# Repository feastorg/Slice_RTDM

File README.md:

# Slice RTDM

Slice for RTD (resistive temperature device) measurement using the MAX31865 chip.

## Introduction

[Short introduction on the project.]

## Usage

[Explain how to use the project. Include examples and screenshots if applicable.]

## Documentation

Please refer to the [docs](/docs) for more info.

---

<div align="center">
  
</div>

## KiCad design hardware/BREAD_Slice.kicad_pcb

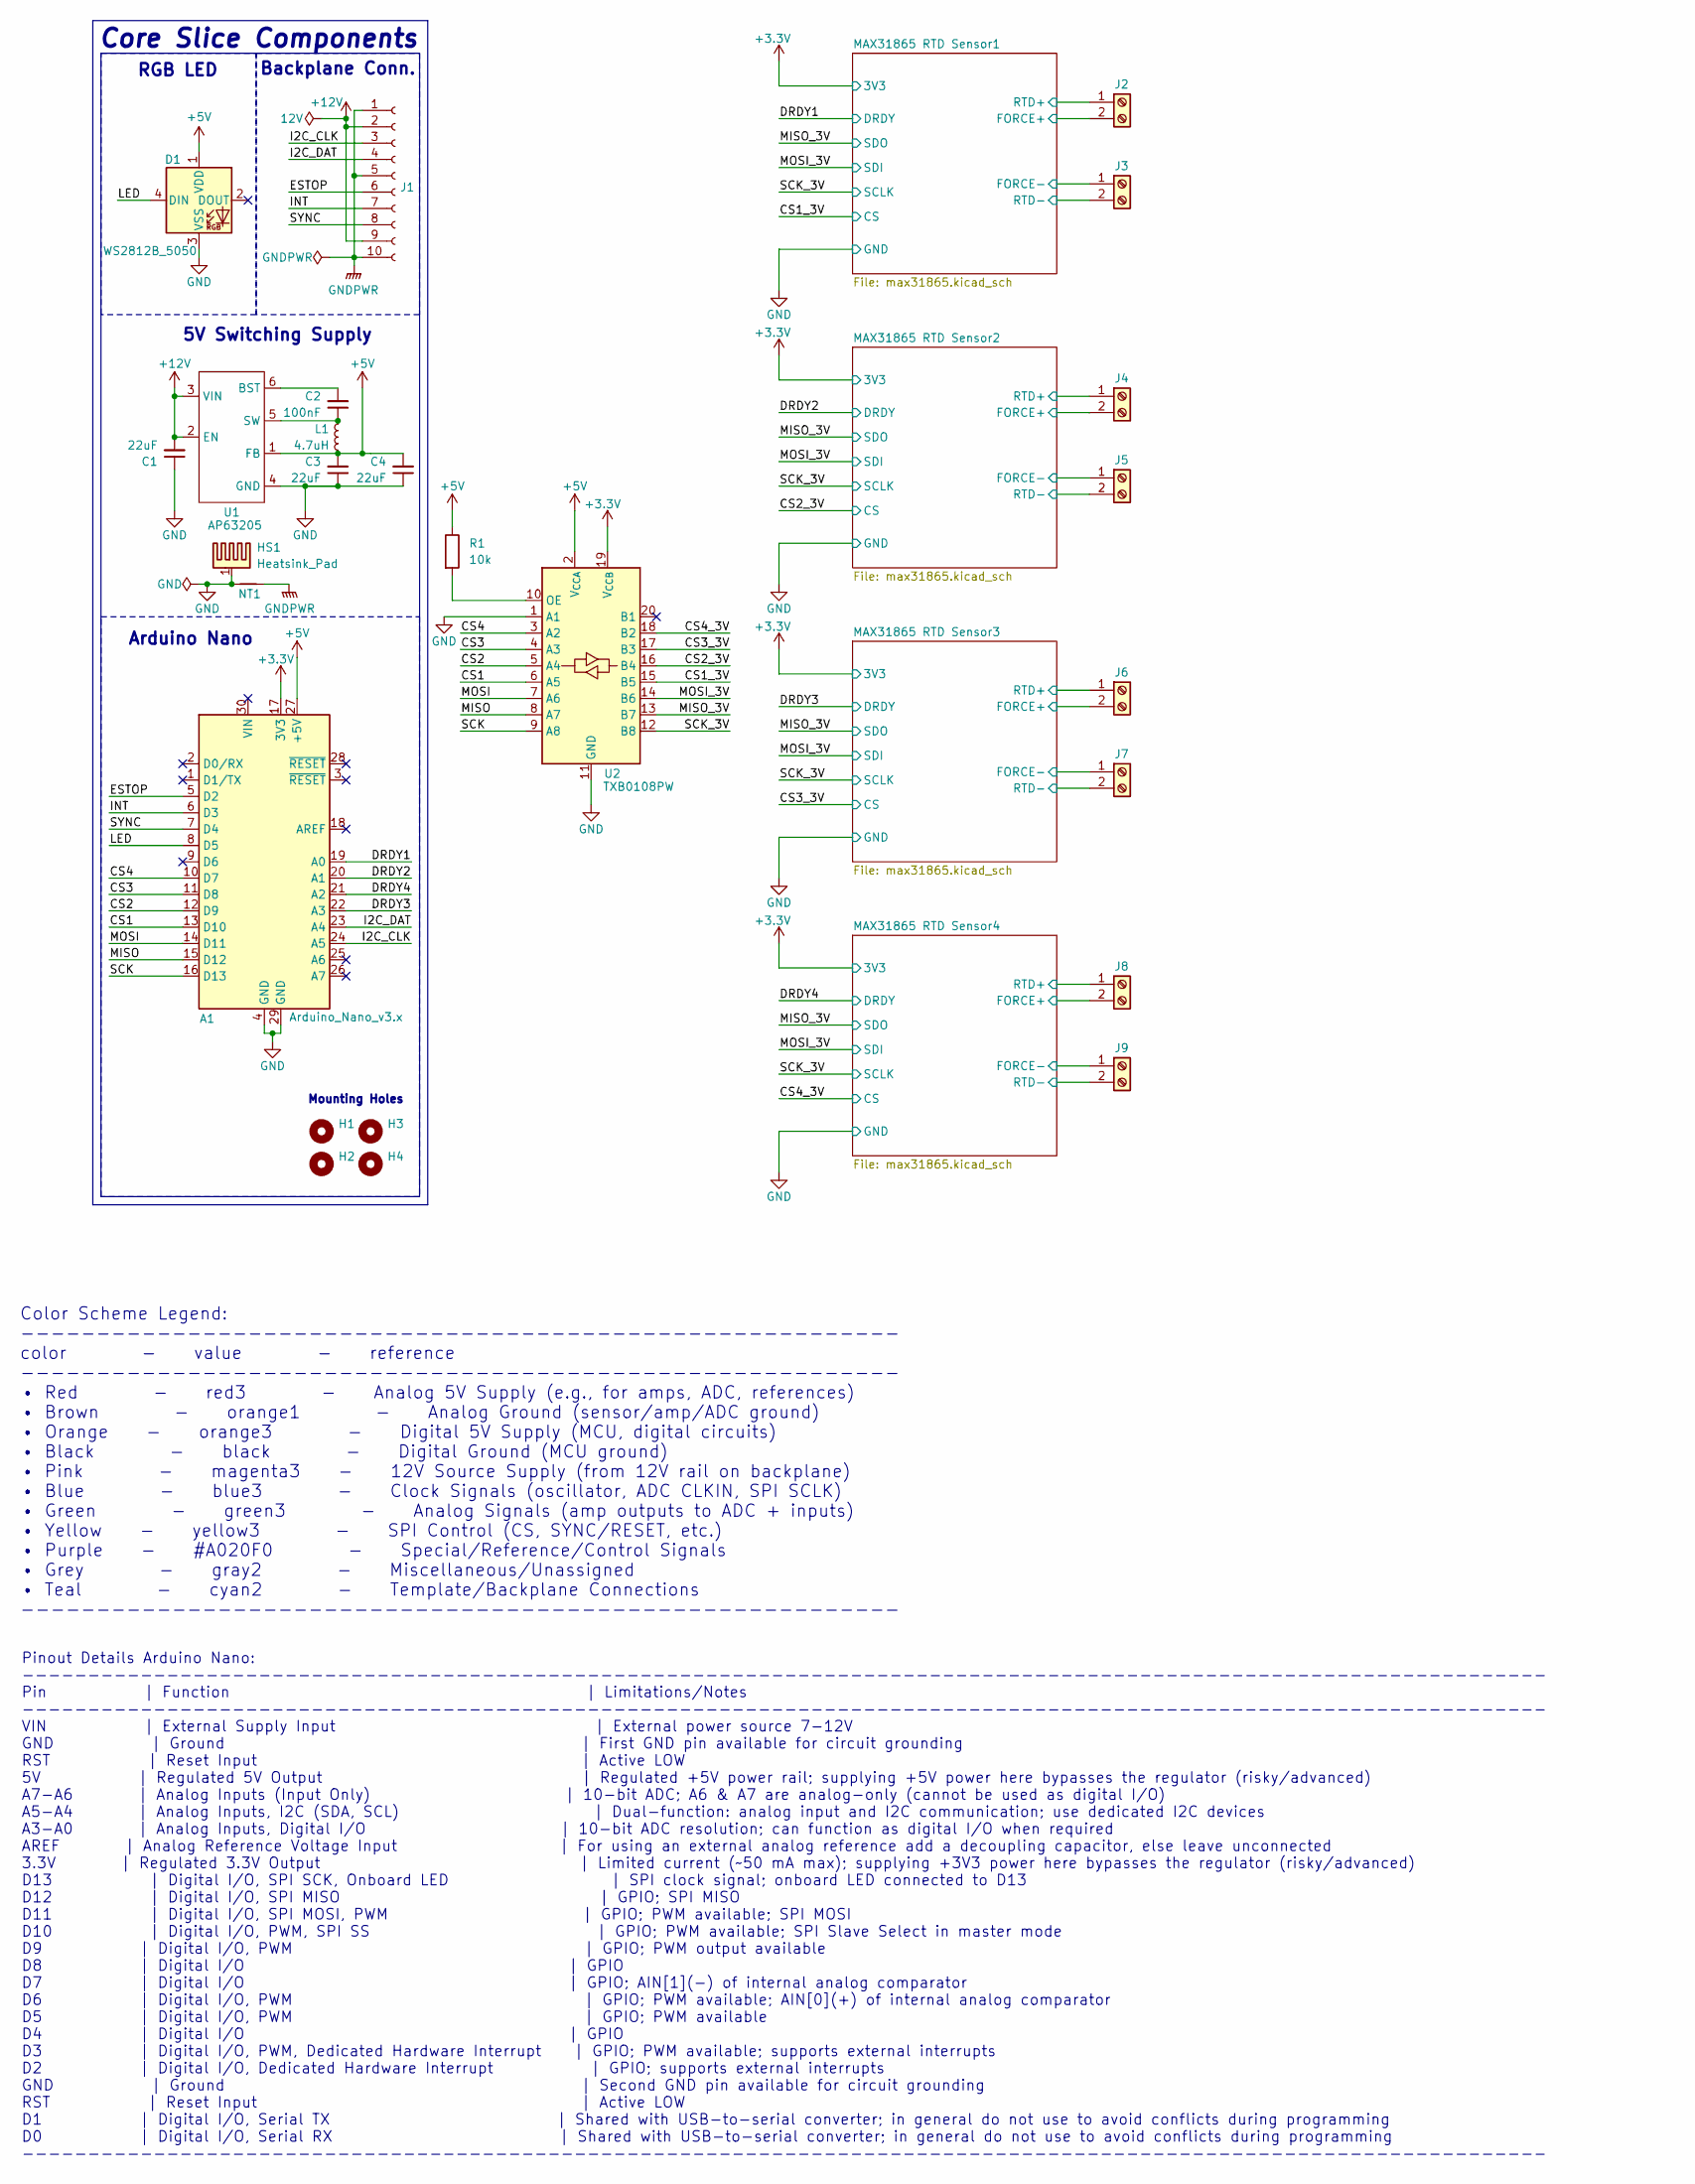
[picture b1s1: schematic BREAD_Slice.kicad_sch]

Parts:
A1: Arduino_Nano_v3.x; Arduino_Nano_Headers
C1, C3, C4: 22uF; C_1206_3216Metric
C2: 100nF; C_1206_3216Metric
D1: WS2812B_5050; WS2812-5050-4PIN
H1, H2, H3, H4: MountingHole; MountingHole_5mm
HS1: Heatsink_Pad; Thermal_Pad
J1: Conn_01x10_Female; PinSocket_1x10_P2.54mm_Horizontal
J2, J3, J4, J5, J6, J7, J8, J9: Screw_Terminal_01x02; TerminalBlock_4Ucon_1x02_P3.50mm_Horizontal
L1: 4.7uH; L_1210_3225Metric
NT1: NetTie_2; NetTie-2_SMD_Pad2.0mm
R1: 10k; R_0805_2012Metric_Pad1.20x1.40mm_HandSolder
U1: AP63205; SOIC_05WU-7_DIO
U2: TXB0108PW; TSSOP-20_4.4x6.5mm_P0.65mm

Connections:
+3.3V: A1.17 (3V3), U2.19 (V_{CCB}); also elsewhere on the board
+5V: A1.27 (+5V), C3.2, C4.2, D1.1 (VDD), L1.2, R1.1, U1.1 (FB), U2.2 (V_{CCA})
+12V: C1.2, J1.2, J1.9, U1.2 (EN), U1.3 (VIN)
/CS1: A1.13 (D10), U2.6 (A5)
/CS1_3V: U2.15 (B5); also elsewhere on the board
/CS2: A1.12 (D9), U2.5 (A4)
/CS2_3V: U2.16 (B4); also elsewhere on the board
/CS3: A1.11 (D8), U2.4 (A3)
/CS3_3V: U2.17 (B3); also elsewhere on the board
/CS4: A1.10 (D7), U2.3 (A2)
/CS4_3V: U2.18 (B2); also elsewhere on the board
/DRDY1: A1.19 (A0); also elsewhere on the board
/DRDY2: A1.20 (A1); also elsewhere on the board
/DRDY3: A1.22 (A3); also elsewhere on the board
/DRDY4: A1.21 (A2); also elsewhere on the board
/ESTOP: A1.5 (D2), J1.6
/I2C_CLK: A1.24 (A5), J1.3
/I2C_DAT: A1.23 (A4), J1.4
/INT: A1.6 (D3), J1.7
/LED: A1.8 (D5), D1.4 (DIN)
/MAX31865 RTD Sensor1/FORCE+: J2.2; also elsewhere on the board
/MAX31865 RTD Sensor1/FORCE-: J3.1; also elsewhere on the board
/MAX31865 RTD Sensor1/RTD+: J2.1; also elsewhere on the board
/MAX31865 RTD Sensor1/RTD-: J3.2; also elsewhere on the board
/MAX31865 RTD Sensor2/FORCE+: J4.2; also elsewhere on the board
/MAX31865 RTD Sensor2/FORCE-: J5.1; also elsewhere on the board
/MAX31865 RTD Sensor2/RTD+: J4.1; also elsewhere on the board
/MAX31865 RTD Sensor2/RTD-: J5.2; also elsewhere on the board
/MAX31865 RTD Sensor3/FORCE+: J6.2; also elsewhere on the board
/MAX31865 RTD Sensor3/FORCE-: J7.1; also elsewhere on the board
/MAX31865 RTD Sensor3/RTD+: J6.1; also elsewhere on the board
/MAX31865 RTD Sensor3/RTD-: J7.2; also elsewhere on the board
/MAX31865 RTD Sensor4/FORCE+: J8.2; also elsewhere on the board
/MAX31865 RTD Sensor4/FORCE-: J9.1; also elsewhere on the board
/MAX31865 RTD Sensor4/RTD+: J8.1; also elsewhere on the board
/MAX31865 RTD Sensor4/RTD-: J9.2; also elsewhere on the board
/MISO: A1.15 (D12), U2.8 (A7)
/MISO_3V: U2.13 (B7); also elsewhere on the board
/MOSI: A1.14 (D11), U2.7 (A6)
/MOSI_3V: U2.14 (B6); also elsewhere on the board
/SCK: A1.16 (D13), U2.9 (A8)
/SCK_3V: U2.12 (B8); also elsewhere on the board
/SYNC: A1.7 (D4), J1.8
GND: A1.4 (GND), A1.29 (GND), C1.1, C3.1, C4.1, D1.3 (VSS), HS1.1, NT1.1, U1.4 (GND), U2.1 (A1), U2.11 (GND); also elsewhere on the board
GNDPWR: J1.1, J1.5, J1.10, NT1.2
unnamed: C2.2, U1.6 (BST)
unnamed: C2.1, L1.1, U1.5 (SW)
unnamed: R1.2, U2.10 (OE)

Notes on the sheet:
5V Switching Supply
Pinout Details Arduino Nano: -------------------------------------------------------------------------------------------------------------------- Pin | Function | Limitations/Notes -------------------------------------------------------------------------------------------------------------------- V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
RGB LED
Color Scheme Legend: ---------------------------------------------------------- color - value - reference ---------------------------------------------------------- • Red - red3 - Analog 5V Supply (e.g., for amps, ADC, references) • Brown - orange1 - Analog Ground (sensor/amp/ADC ground) • Orange -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
Core Slice Components
Arduino Nano
Mounting Holes
Backplane Conn.

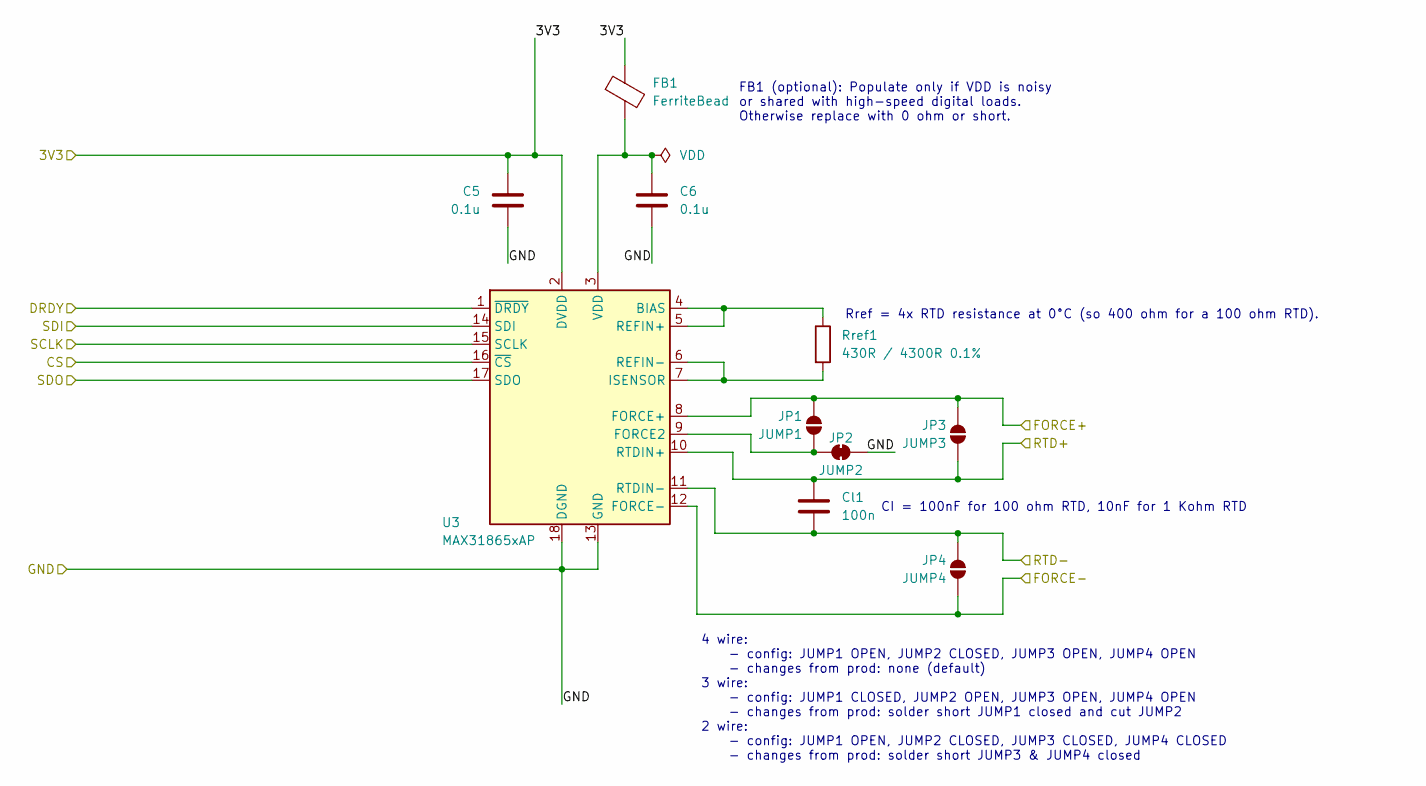
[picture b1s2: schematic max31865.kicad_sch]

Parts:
C5, C6: 0.1u; C_0805_2012Metric_Pad1.18x1.45mm_HandSolder
Cl1: 100n; C_0805_2012Metric_Pad1.18x1.45mm_HandSolder
FB1: FerriteBead; R_0805_2012Metric_Pad1.20x1.40mm_HandSolder
JP1: JUMP1; SolderJumper-2_P1.3mm_Open_TrianglePad1.0x1.5mm
JP2: JUMP2; SolderJumper-2_P1.3mm_Bridged_RoundedPad1.0x1.5mm
JP3: JUMP3; SolderJumper-2_P1.3mm_Open_TrianglePad1.0x1.5mm
JP4: JUMP4; SolderJumper-2_P1.3mm_Open_TrianglePad1.0x1.5mm
Rref1: 430R / 4300R 0.1%; R_0805_2012Metric_Pad1.20x1.40mm_HandSolder
U3: MAX31865xAP; SSOP-20_5.3x7.2mm_P0.65mm

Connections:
+3.3V: C5.1, FB1.1, U3.2 (DVDD); also elsewhere on the board
/CS1_3V: U3.16 (~CS); also elsewhere on the board
/DRDY1: U3.1 (~DRDY); also elsewhere on the board
/MAX31865 RTD Sensor1/FORCE+: JP1.2 (B), JP3.2 (B), U3.8 (FORCE+); also elsewhere on the board
/MAX31865 RTD Sensor1/FORCE-: JP4.1 (A), U3.12 (FORCE-); also elsewhere on the board
/MAX31865 RTD Sensor1/RTD+: Cl1.1, JP3.1 (A), U3.10 (RTDIN+); also elsewhere on the board
/MAX31865 RTD Sensor1/RTD-: Cl1.2, JP4.2 (B), U3.11 (RTDIN-); also elsewhere on the board
/MISO_3V: U3.17 (SDO); also elsewhere on the board
/MOSI_3V: U3.14 (SDI); also elsewhere on the board
/SCK_3V: U3.15 (SCLK); also elsewhere on the board
GND: C5.2, C6.2, JP2.1 (A), U3.13 (GND), U3.18 (DGND), U3.19 (GND); also elsewhere on the board
unnamed: JP1.1 (A), JP2.2 (B), U3.9 (FORCE2)
unnamed: Rref1.1, U3.4 (BIAS), U3.5 (REFIN+)
unnamed: Rref1.2, U3.6 (REFIN-), U3.7 (ISENSOR)
unnamed: C6.1, FB1.2, U3.3 (VDD)

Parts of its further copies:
C7, C8, C9, C10, C11, C12: 0.1u; C_0805_2012Metric_Pad1.18x1.45mm_HandSolder
Cl2, Cl3, Cl4: 100n; C_0805_2012Metric_Pad1.18x1.45mm_HandSolder
FB2, FB3, FB4: FerriteBead; R_0805_2012Metric_Pad1.20x1.40mm_HandSolder
JP5, JP9, JP13: JUMP1; SolderJumper-2_P1.3mm_Open_TrianglePad1.0x1.5mm
JP6, JP10, JP14: JUMP2; SolderJumper-2_P1.3mm_Bridged_RoundedPad1.0x1.5mm
JP7, JP11, JP15: JUMP3; SolderJumper-2_P1.3mm_Open_TrianglePad1.0x1.5mm
JP8, JP12, JP16: JUMP4; SolderJumper-2_P1.3mm_Open_TrianglePad1.0x1.5mm
Rref2, Rref3, Rref4: 430R / 4300R 0.1%; R_0805_2012Metric_Pad1.20x1.40mm_HandSolder
U4, U5, U6: MAX31865xAP; SSOP-20_5.3x7.2mm_P0.65mm

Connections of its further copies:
+3.3V: C7.1, C9.1, C11.1, FB2.1, FB3.1, FB4.1, U4.2 (DVDD), U5.2 (DVDD), U6.2 (DVDD); also elsewhere on the board
/CS2_3V: U5.16 (~CS); also elsewhere on the board
/CS3_3V: U4.16 (~CS); also elsewhere on the board
/CS4_3V: U6.16 (~CS); also elsewhere on the board
/DRDY2: U5.1 (~DRDY); also elsewhere on the board
/DRDY3: U4.1 (~DRDY); also elsewhere on the board
/DRDY4: U6.1 (~DRDY); also elsewhere on the board
/MAX31865 RTD Sensor2/FORCE+: JP9.2 (B), JP11.2 (B), U5.8 (FORCE+); also elsewhere on the board
/MAX31865 RTD Sensor2/FORCE-: JP12.1 (A), U5.12 (FORCE-); also elsewhere on the board
/MAX31865 RTD Sensor2/RTD+: Cl3.1, JP11.1 (A), U5.10 (RTDIN+); also elsewhere on the board
/MAX31865 RTD Sensor2/RTD-: Cl3.2, JP12.2 (B), U5.11 (RTDIN-); also elsewhere on the board
/MAX31865 RTD Sensor3/FORCE+: JP5.2 (B), JP7.2 (B), U4.8 (FORCE+); also elsewhere on the board
/MAX31865 RTD Sensor3/FORCE-: JP8.1 (A), U4.12 (FORCE-); also elsewhere on the board
/MAX31865 RTD Sensor3/RTD+: Cl2.1, JP7.1 (A), U4.10 (RTDIN+); also elsewhere on the board
/MAX31865 RTD Sensor3/RTD-: Cl2.2, JP8.2 (B), U4.11 (RTDIN-); also elsewhere on the board
/MAX31865 RTD Sensor4/FORCE+: JP13.2 (B), JP15.2 (B), U6.8 (FORCE+); also elsewhere on the board
/MAX31865 RTD Sensor4/FORCE-: JP16.1 (A), U6.12 (FORCE-); also elsewhere on the board
/MAX31865 RTD Sensor4/RTD+: Cl4.1, JP15.1 (A), U6.10 (RTDIN+); also elsewhere on the board
/MAX31865 RTD Sensor4/RTD-: Cl4.2, JP16.2 (B), U6.11 (RTDIN-); also elsewhere on the board
/MISO_3V: U4.17 (SDO), U5.17 (SDO), U6.17 (SDO); also elsewhere on the board
/MOSI_3V: U4.14 (SDI), U5.14 (SDI), U6.14 (SDI); also elsewhere on the board
/SCK_3V: U4.15 (SCLK), U5.15 (SCLK), U6.15 (SCLK); also elsewhere on the board
GND: C7.2, C8.2, C9.2, C10.2, C11.2, C12.2, JP6.1 (A), JP10.1 (A), JP14.1 (A), U4.13 (GND), U4.18 (DGND), U4.19 (GND), U5.13 (GND), U5.18 (DGND), U5.19 (GND), U6.13 (GND), U6.18 (DGND), U6.19 (GND); also elsewhere on the board
unnamed: JP5.1 (A), JP6.2 (B), U4.9 (FORCE2)
unnamed: JP9.1 (A), JP10.2 (B), U5.9 (FORCE2)
unnamed: JP13.1 (A), JP14.2 (B), U6.9 (FORCE2)
unnamed: Rref2.1, U4.4 (BIAS), U4.5 (REFIN+)
unnamed: Rref2.2, U4.6 (REFIN-), U4.7 (ISENSOR)
unnamed: C8.1, FB2.2, U4.3 (VDD)
unnamed: Rref3.1, U5.4 (BIAS), U5.5 (REFIN+)
unnamed: Rref3.2, U5.6 (REFIN-), U5.7 (ISENSOR)
unnamed: C10.1, FB3.2, U5.3 (VDD)
unnamed: Rref4.1, U6.4 (BIAS), U6.5 (REFIN+)
unnamed: Rref4.2, U6.6 (REFIN-), U6.7 (ISENSOR)
unnamed: C12.1, FB4.2, U6.3 (VDD)

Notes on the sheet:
FB1 (optional): Populate only if VDD is noisy or shared with high-speed digital loads. Otherwise replace with 0 ohm or short.
4 wire: - config: JUMP1 OPEN, JUMP2 CLOSED, JUMP3 OPEN, JUMP4 OPEN - changes from prod: none (default) 3 wire: - config: JUMP1 CLOSED, JUMP2 OPEN, JUMP3 OPEN, JUMP4 OPEN - changes from prod: solder short JUMP1 closed and cut JUMP2 2 wire: - config: JUMP1 OPEN, JUMP2 CLOSED, JUMP3 CLOSED, JUMP4 CLOS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
CI = 100nF for 100 ohm RTD, 10nF for 1 Kohm RTD
Rref = 4x RTD resistance at 0°C (so 400 ohm for a 100 ohm RTD).

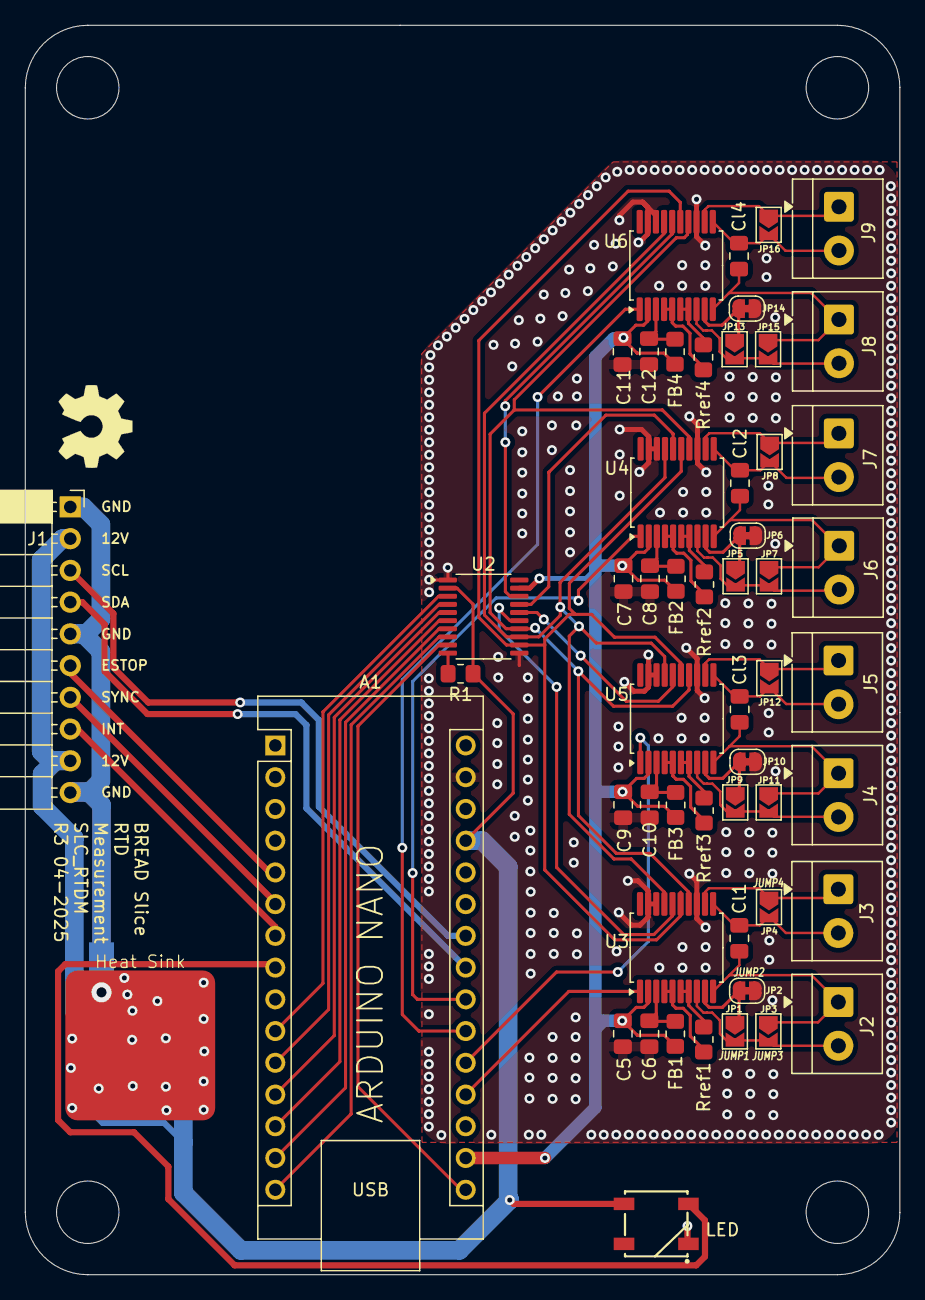
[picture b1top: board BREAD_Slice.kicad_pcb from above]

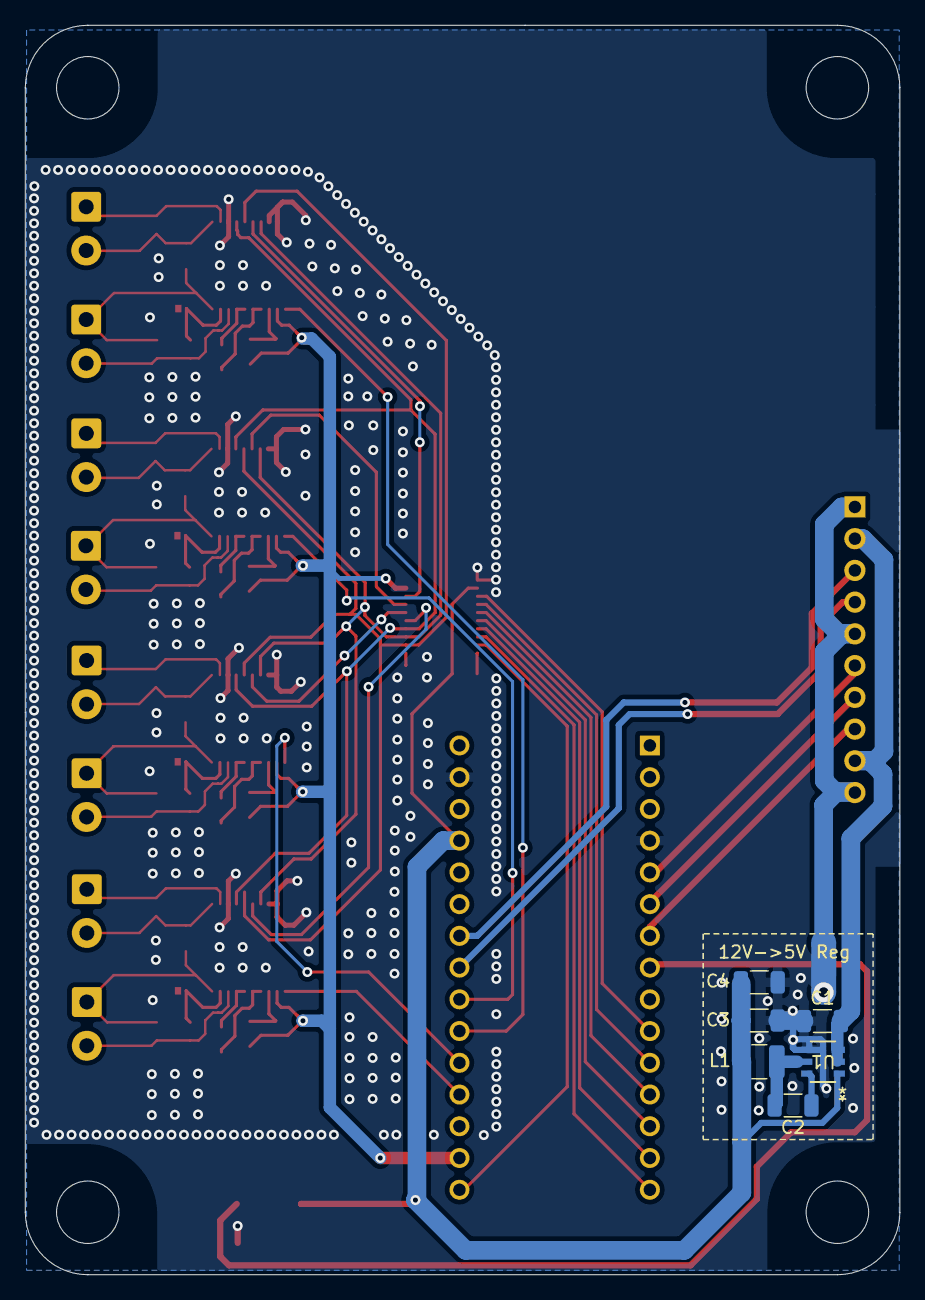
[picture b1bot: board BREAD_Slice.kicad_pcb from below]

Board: 2 copper layers, 70.0 x 100.0 mm, 66 parts (7 on the bottom side), 64 nets.

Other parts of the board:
Logo1: Logo_Open_Hardware_Small; OSHW-Symbol_6.7x6mm_SilkScreen

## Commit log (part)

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2025-04-14 initial commit, max31865 sub sheet done
2025-04-15 initial commit, complete schematic and board
2025-04-17 updated docs
2026-01-22 review and revise board to use kmlib properly and clear drc/erc
2026-05-20 Add slice.yaml manifest (schema v1.0)
2026-05-24 Add KiBot/docs pipeline
2026-05-24 📄 KiBot index + board renders (auto)
2026-05-24 TODO: all CI green
2026-05-24 Standardize TODO.md with Pass 1/Pass 2 structure
